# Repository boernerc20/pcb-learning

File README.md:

# PCB Designs
These designs are based on projects from KiCad Like a Pro (Edition 4). While the schematics and overall board outlines follow the textbook closely, all routing, component selection, and placement were done independently.

## Beginner Design: Breadboard Power Supply
This PCB is a compact dual-voltage breadboard power supply designed to deliver 5V and 3.3V from a 6–12V wall adapter. It connects directly to a mini breadboard via pin headers and includes onboard voltage regulators (LM317 and LM7805), a barrel jack input, and selectable outputs—all laid out with through-hole components for easy assembly.

**3D-View:**
<table>
  <tr>
    <td>
      
    </td>
    <td>
      
    </td>
  </tr>
</table>

**Schematic:**
<table>
  <tr>
    <td>
      
    </td>
  </tr>
</table>

**Layout:**
<table>
  <tr>
    <td>
      
    </td>
  </tr>
</table>

## Intermediate Design: Solar Power Regulator
This PCB is a solar-powered 3.3V boost converter based on Clemens Valens’ Tiny Solar Supply, originally published by Elektor. Designed in KiCad, it steps up the voltage from a small solar panel and rechargeable battery using the AP3015 IC—ideal for powering low-power microcontrollers.

**3D-View:**
<table>
  <tr>
    <td>
      
    </td>
    <td>
      
    </td>
  </tr>
</table>

**Schematic:**
<table>
  <tr>
    <td>
      
    </td>
  </tr>
</table>

**Layout:**
<table>
  <tr>
    <td>
      
    </td>
  </tr>
</table>

## Advanced Design: ESP32 Clone
This ESP32 development board is based on Espressif’s official reference design for the DevKitC-V4. I followed the original schematic and layout closely, using KiCad for all design work and customizing the footprint placement and component sizing for easier hand assembly/soldering. This project emphasizes working from manufacturer reference designs and practicing dense PCB layout techniques.

**3D-View:**
<table>
  <tr>
    <td>
      
    </td>
    <td>
      
    </td>
  </tr>
</table>

**Schematic:**
<table>
  <tr>
    <td>
      
    </td>
  </tr>
</table>

**Layout:**
<table>
  <tr>
    <td>
      
    </td>
  </tr>
</table>

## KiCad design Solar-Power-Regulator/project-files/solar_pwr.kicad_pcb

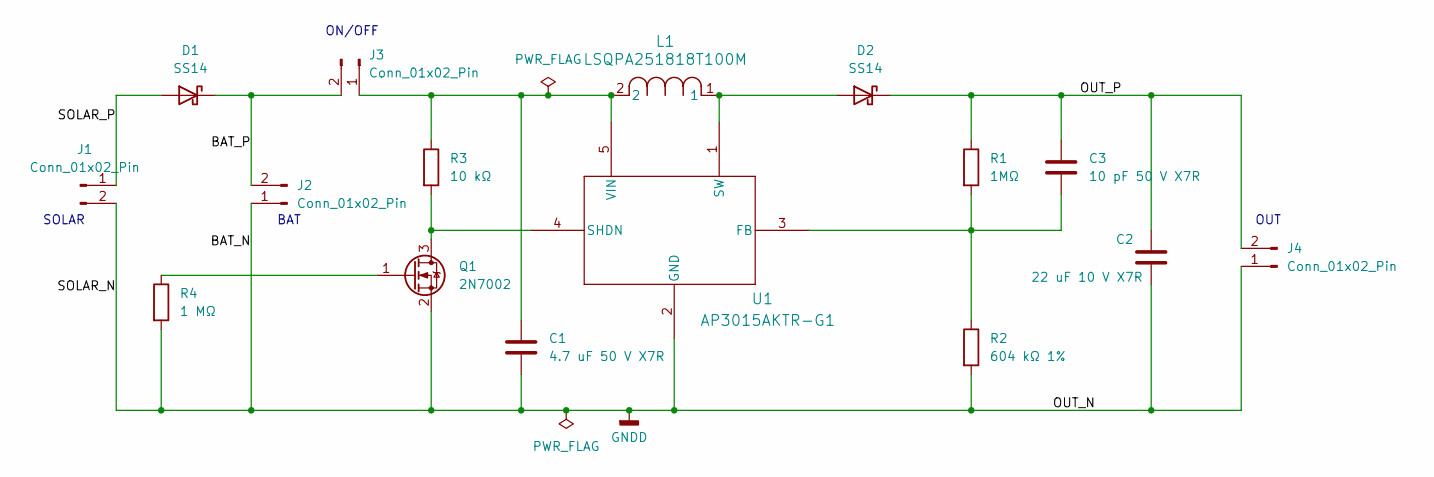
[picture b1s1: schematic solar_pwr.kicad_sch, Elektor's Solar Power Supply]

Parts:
C1: 4.7 uF 50 V X7R; C_0805_2012Metric
C2: 22 uF 10 V X7R; C_1206_3216Metric
C3: 10 pF 50 V X7R; C_0805_2012Metric
D1, D2: SS14; D_SMA
J1, J2, J3: Conn_01x02_Pin; PinHeader_1x02_P2.54mm_Vertical
J4: Conn_01x02_Pin; PinHeader_1x02_P2.00mm_Horizontal
L1: LSQPA251818T100M; IND_LSQPA2518_TAY
Q1: 2N7002; SOT-23
R1: 1MΩ; R_0805_2012Metric
R2: 604 kΩ 1%; R_0805_2012Metric
R3: 10 kΩ; R_0805_2012Metric
R4: 1 MΩ; R_0805_2012Metric
U1: AP3015AKTR-G1; SOT23-5_1P55X2P9_DIO

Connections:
/BAT_P: D1.1 (K), J2.2, J3.2
/OUT_P: C2.1, C3.1, D2.1 (K), J4.2, R1.1
/SOLAR_P: D1.2 (A), J1.1
GNDD: C1.2, C2.2, J1.2, J2.1, J4.1, Q1.2 (S), R2.2, R4.2, U1.2 (GND)
unnamed: D2.2 (A), L1.1, U1.1 (SW)
unnamed: C1.1, J3.1, L1.2, R3.1, U1.5 (VIN)
unnamed: Q1.3 (D), R3.2, U1.4 (SHDN)
unnamed: Q1.1 (G), R4.1
unnamed: C3.2, R1.2, R2.1, U1.3 (FB)

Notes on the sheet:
OUT
SOLAR
ON/OFF
BAT

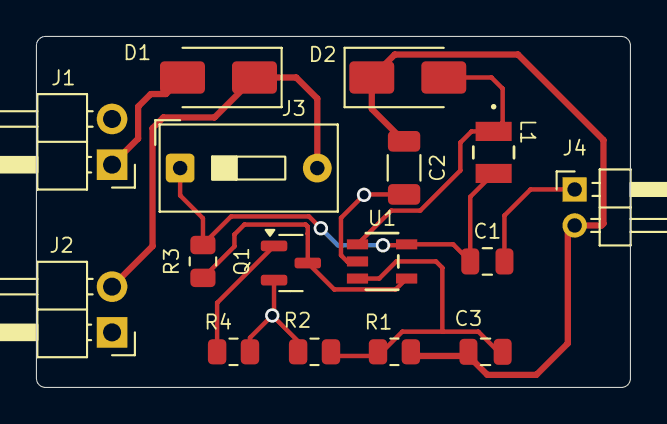
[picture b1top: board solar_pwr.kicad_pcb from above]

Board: 2 copper layers, 33.0 x 19.5 mm, 16 parts (0 on the bottom side), 9 nets.

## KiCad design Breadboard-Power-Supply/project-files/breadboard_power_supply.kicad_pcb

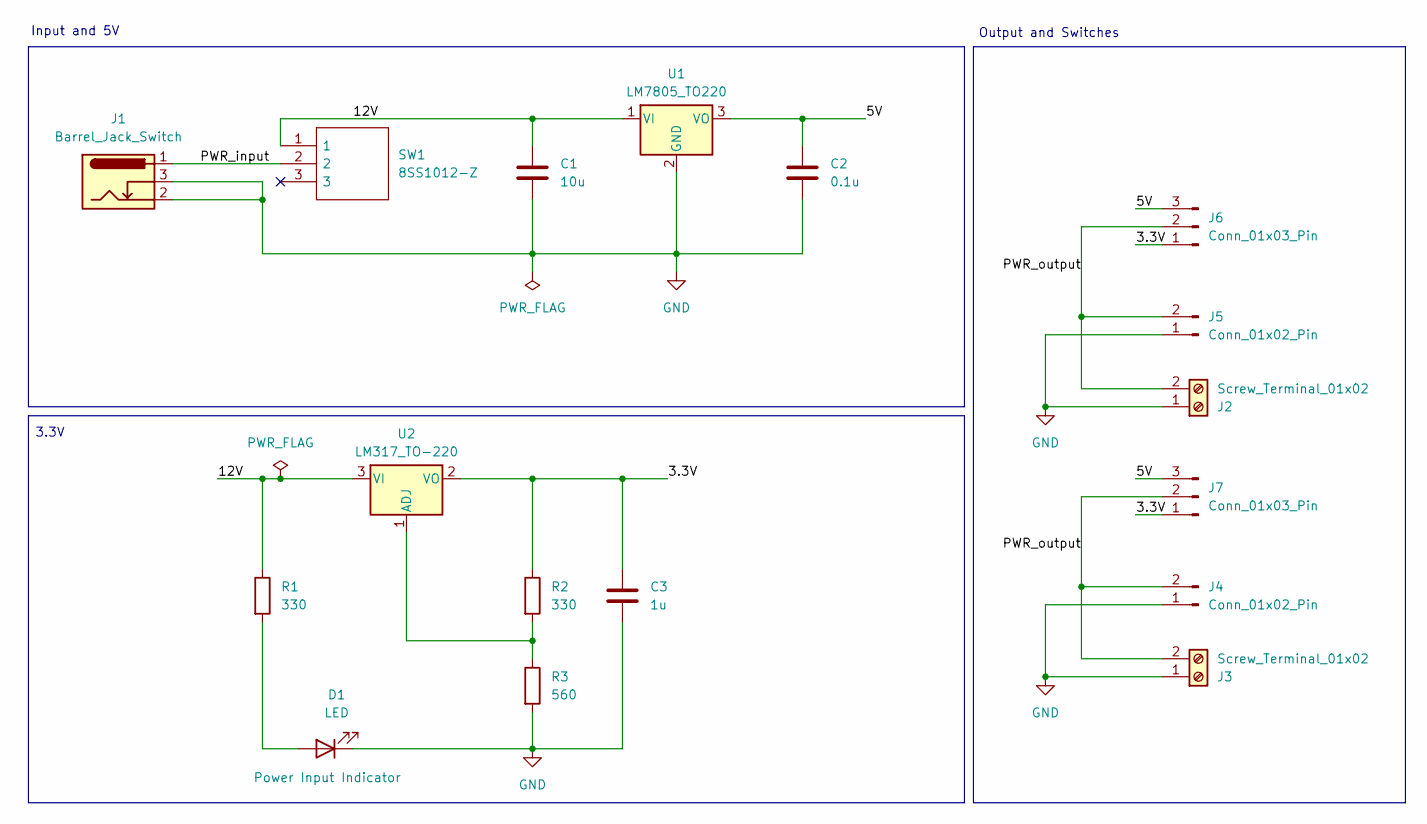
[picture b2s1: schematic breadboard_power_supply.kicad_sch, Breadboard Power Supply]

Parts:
C1: 10u; C_Disc_D3.0mm_W1.6mm_P2.50mm
C2: 0.1u; C_Disc_D3.0mm_W1.6mm_P2.50mm
C3: 1u; C_Disc_D3.0mm_W1.6mm_P2.50mm
D1: LED; LED_D5.0mm
J1: Barrel_Jack_Switch; BarrelJack_Horizontal
J2, J3: Screw_Terminal_01x02; TerminalBlock_bornier-2_P5.08mm
J4, J5: Conn_01x02_Pin; PinHeader_1x02_P2.54mm_Vertical
J6, J7: Conn_01x03_Pin; PinHeader_1x03_P2.54mm_Vertical
R1, R2: 330; R_Axial_DIN0204_L3.6mm_D1.6mm_P7.62mm_Horizontal
R3: 560; R_Axial_DIN0204_L3.6mm_D1.6mm_P7.62mm_Horizontal
SW1: 8SS1012-Z; 8SS1012Z; Manufacturer_Part_Number 8SS1012-Z; Mouser Part Number 229-8SS1012-Z
U1: LM7805_TO220; TO-220-3_Vertical
U2: LM317_TO-220; TO-220-3_Vertical

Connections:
/3.3V: C3.1, J6.1, J7.1, R2.1, U2.2 (VO)
/5V: C2.1, J6.3, J7.3, U1.3 (VO)
/12V: C1.1, R1.1, SW1.1, U1.1 (VI), U2.3 (VI)
/PWR_input: J1.1, SW1.2
/PWR_output: J2.2, J3.2, J4.2, J5.2, J6.2, J7.2
GND: C1.2, C2.2, C3.2, D1.1 (K), J1.2, J1.3, J2.1, J3.1, J4.1, J5.1, R3.2, U1.2 (GND)
unnamed: D1.2 (A), R1.2
unnamed: R2.2, R3.1, U2.1 (ADJ)

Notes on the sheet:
Input and 5V
3.3V
Output and Switches

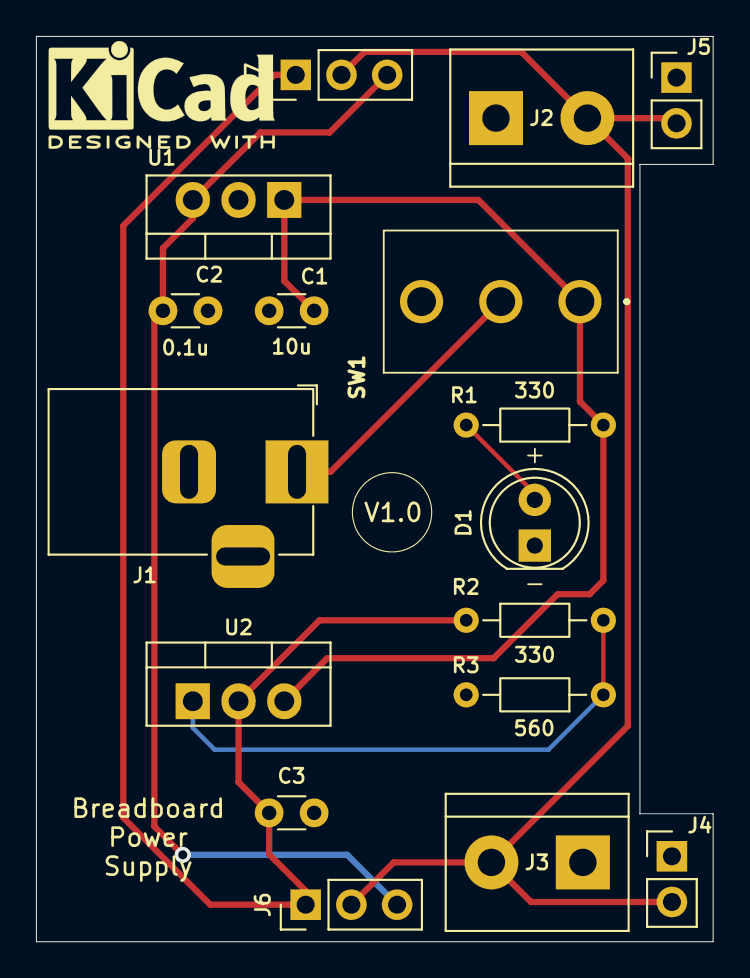
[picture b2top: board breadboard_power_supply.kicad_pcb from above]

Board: 2 copper layers, 37.6 x 50.3 mm, 17 parts (0 on the bottom side), 8 nets.

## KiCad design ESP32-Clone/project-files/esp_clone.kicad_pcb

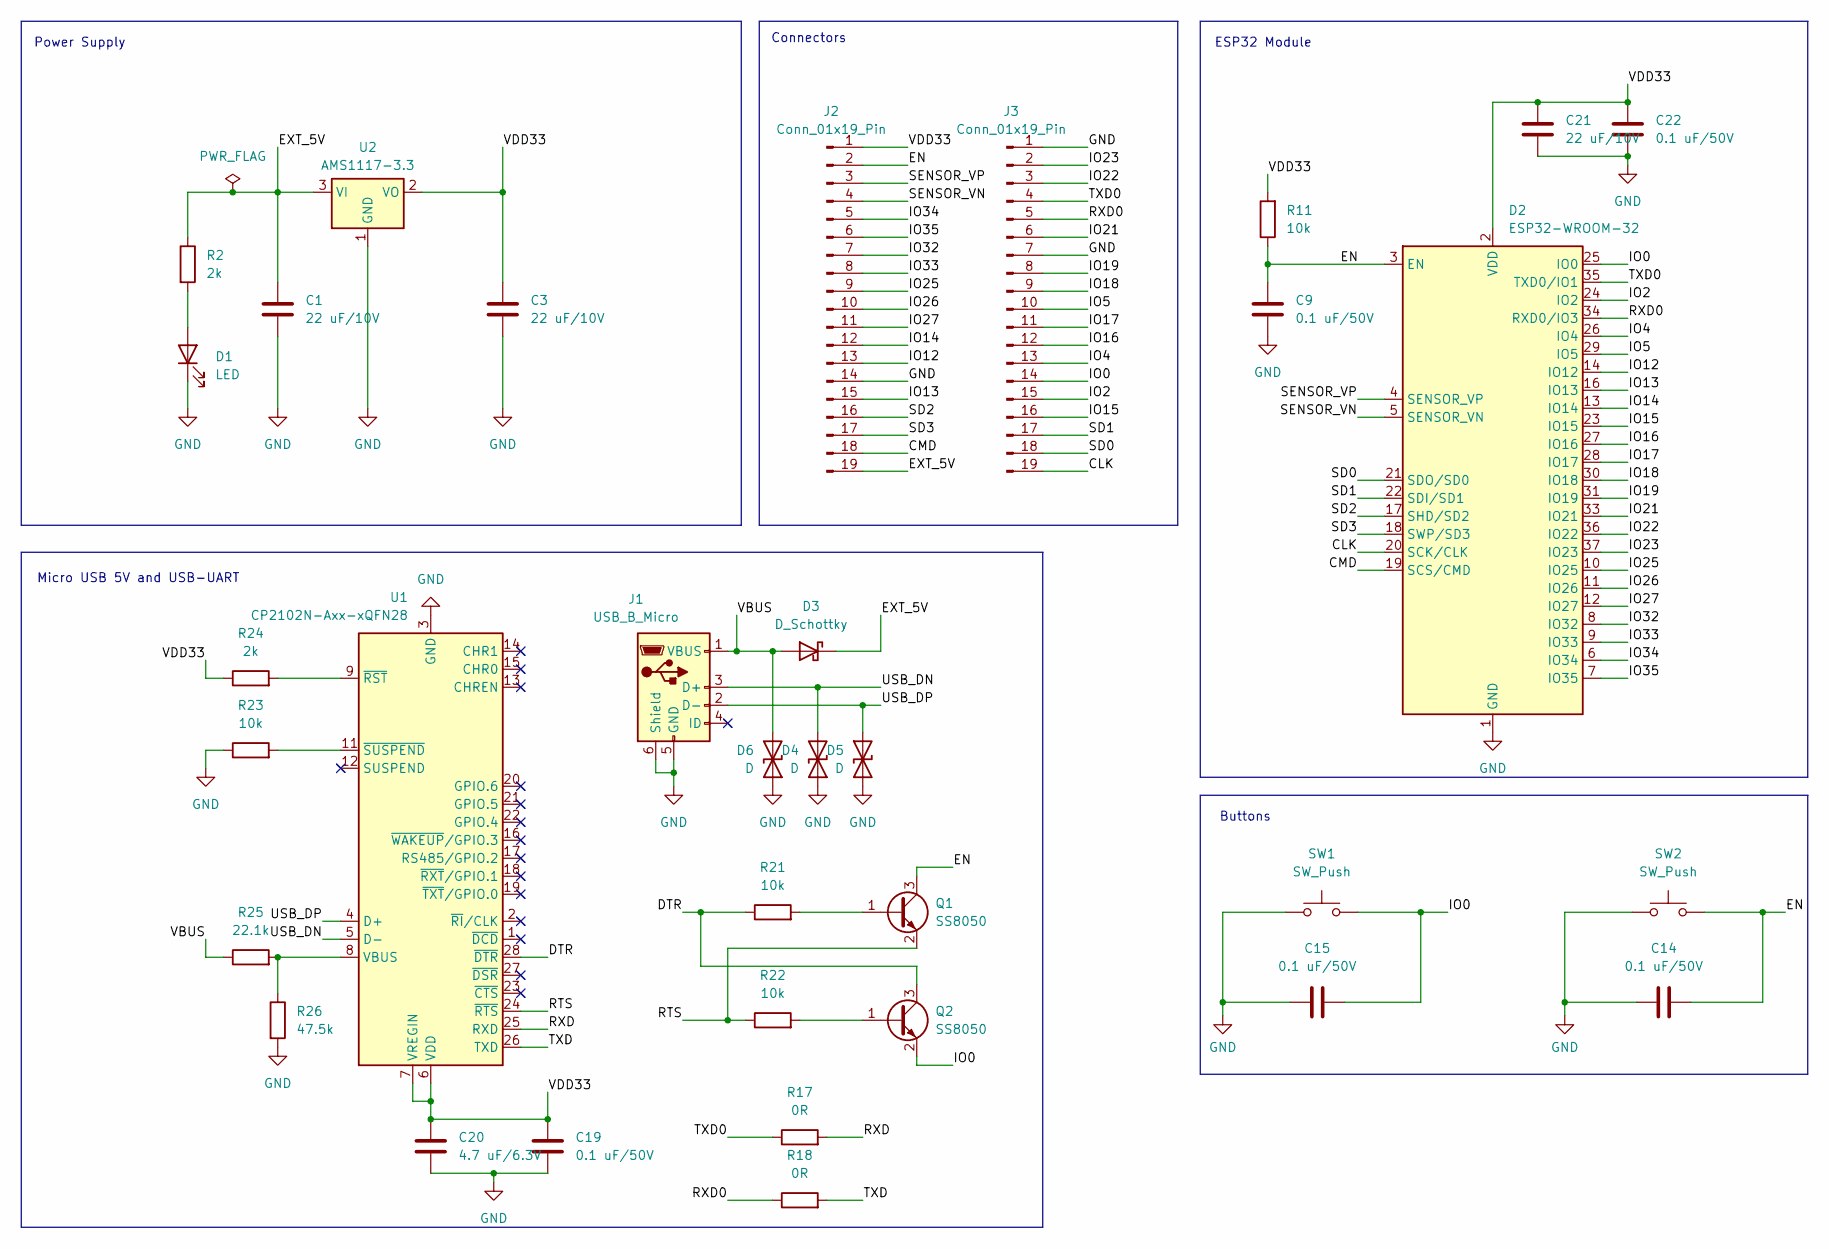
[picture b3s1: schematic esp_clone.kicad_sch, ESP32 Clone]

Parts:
C1, C3, C21: 22 uF/10V; C_0603_1608Metric
C9, C14, C15, C19, C22: 0.1 uF/50V; C_0402_1005Metric
C20: 4.7 uF/6.3V; C_0402_1005Metric
D1: LED; LED_0603_1608Metric
D2: ESP32-WROOM-32
D3: D_Schottky; D_SOD-323F
D4, D5, D6: D; D_SOD-523
J1: USB_B_Micro; USB_Micro-AB_Molex_47590-0001
J2, J3: Conn_01x19_Pin; PinHeader_1x19_P2.54mm_Vertical
Q1, Q2: SS8050; SOT-23
R2, R24: 2k; R_0402_1005Metric
R11, R21, R22, R23: 10k; R_0402_1005Metric
R17, R18: 0R; R_0402_1005Metric
R25: 22.1k; R_0402_1005Metric
R26: 47.5k; R_0402_1005Metric
SW1, SW2: SW_Push; SW_SPST_B3U-1100P
U1: CP2102N-Axx-xQFN28; QFN-28-1EP_5x5mm_P0.5mm_EP3.35x3.35mm
U2: AMS1117-3.3; SOT-223-3_TabPin2

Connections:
/CLK: D2.20 (SCK/CLK), J3.19
/CMD: D2.19 (SCS/CMD), J2.18
/DTR: Q2.3 (C), R21.1, U1.28 (~DTR)
/EN: C9.1, C14.2, D2.3 (EN), J2.2, Q1.3 (C), R11.1, SW2.2
/EXT_5V: C1.1, D3.1 (K), J2.19, R2.1, U2.3 (VI)
/IO0: C15.2, D2.25 (IO0), J3.14, Q2.2 (E), SW1.2
/IO2: D2.24 (IO2), J3.15
/IO4: D2.26 (IO4), J3.13
/IO5: D2.29 (IO5), J3.10
/IO12: D2.14 (IO12), J2.13
/IO13: D2.16 (IO13), J2.15
/IO14: D2.13 (IO14), J2.12
/IO15: D2.23 (IO15), J3.16
/IO16: D2.27 (IO16), J3.12
/IO17: D2.28 (IO17), J3.11
/IO18: D2.30 (IO18), J3.9
/IO19: D2.31 (IO19), J3.8
/IO21: D2.33 (IO21), J3.6
/IO22: D2.36 (IO22), J3.3
/IO23: D2.37 (IO23), J3.2
/IO25: D2.10 (IO25), J2.9
/IO26: D2.11 (IO26), J2.10
/IO27: D2.12 (IO27), J2.11
/IO32: D2.8 (IO32), J2.7
/IO33: D2.9 (IO33), J2.8
/IO34: D2.6 (IO34), J2.5
/IO35: D2.7 (IO35), J2.6
/RTS: Q1.2 (E), R22.1, U1.24 (~RTS)
/RXD: R17.2, U1.25 (RXD)
/RXD0: D2.34 (RXD0/IO3), J3.5, R18.1
/SD0: D2.21 (SDO/SD0), J3.18
/SD1: D2.22 (SDI/SD1), J3.17
/SD2: D2.17 (SHD/SD2), J2.16
/SD3: D2.18 (SWP/SD3), J2.17
/SENSOR_VN: D2.5 (SENSOR_VN), J2.4
/SENSOR_VP: D2.4 (SENSOR_VP), J2.3
/TXD: R18.2, U1.26 (TXD)
/TXD0: D2.35 (TXD0/IO1), J3.4, R17.1
/USB_DN: D4.2 (A2), J1.3 (D+), U1.5 (D-)
/USB_DP: D5.1 (A1), J1.2 (D-), U1.4 (D+)
/VBUS: D3.2 (A), D6.2 (A2), J1.1 (VBUS), R25.1
/VDD33: C3.1, C19.1, C20.1, C21.1, C22.1, D2.2 (VDD), J2.1, R11.2, R24.1, U1.6 (VDD), U1.7 (VREGIN), U2.2 (VO)
GND: C1.2, C3.2, C9.2, C14.1, C15.1, C19.2, C20.2, C21.2, C22.2, D1.1 (K), D2.1 (GND), D2.15 (GND), D2.38 (GND), D2.39 (GND), D4.1 (A1), D5.2 (A2), D6.1 (A1), J1.5 (GND), J1.6 (Shield), J2.14, J3.1, J3.7, R23.1, R26.2, SW1.1, SW2.1, U1.3 (GND), U1.29 (GND), U2.1 (GND)
unnamed: D1.2 (A), R2.2
unnamed: Q1.1 (B), R21.2
unnamed: Q2.1 (B), R22.2
unnamed: R25.2, R26.1, U1.8 (VBUS)
unnamed: R24.2, U1.9 (~RST)
unnamed: R23.2, U1.11 (~SUSPEND)

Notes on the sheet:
Power Supply
Connectors
Micro USB 5V and USB-UART
Buttons
ESP32 Module

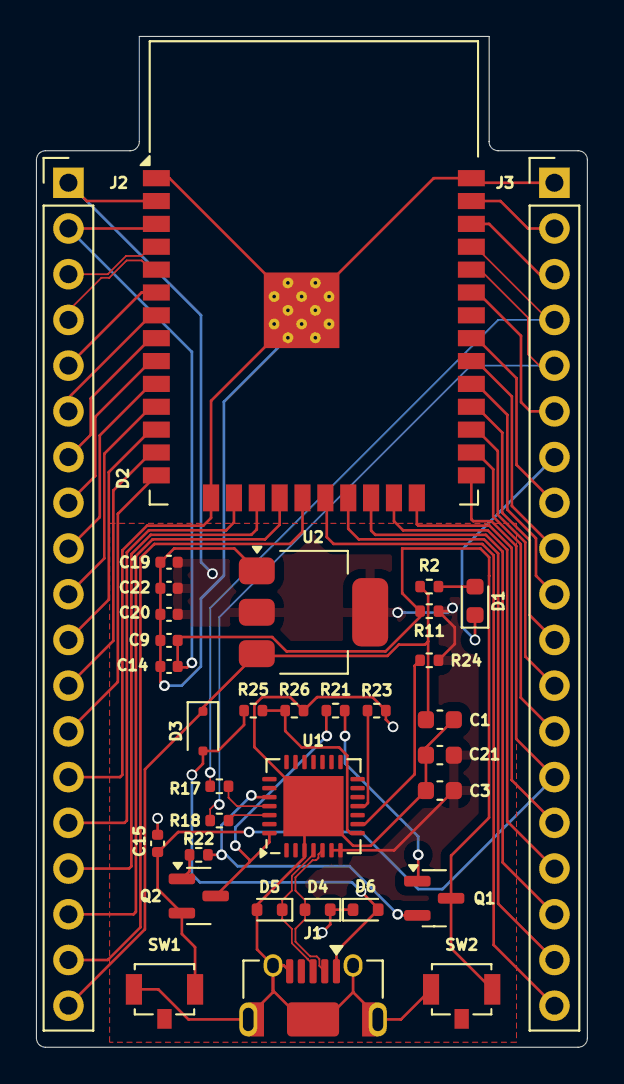
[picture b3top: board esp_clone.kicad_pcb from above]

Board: 2 copper layers, 30.6 x 56.2 mm, 34 parts (0 on the bottom side), 49 nets.

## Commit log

2025-07-16 all three designs
2025-07-16 descriptions
2025-07-16 renamed solar
